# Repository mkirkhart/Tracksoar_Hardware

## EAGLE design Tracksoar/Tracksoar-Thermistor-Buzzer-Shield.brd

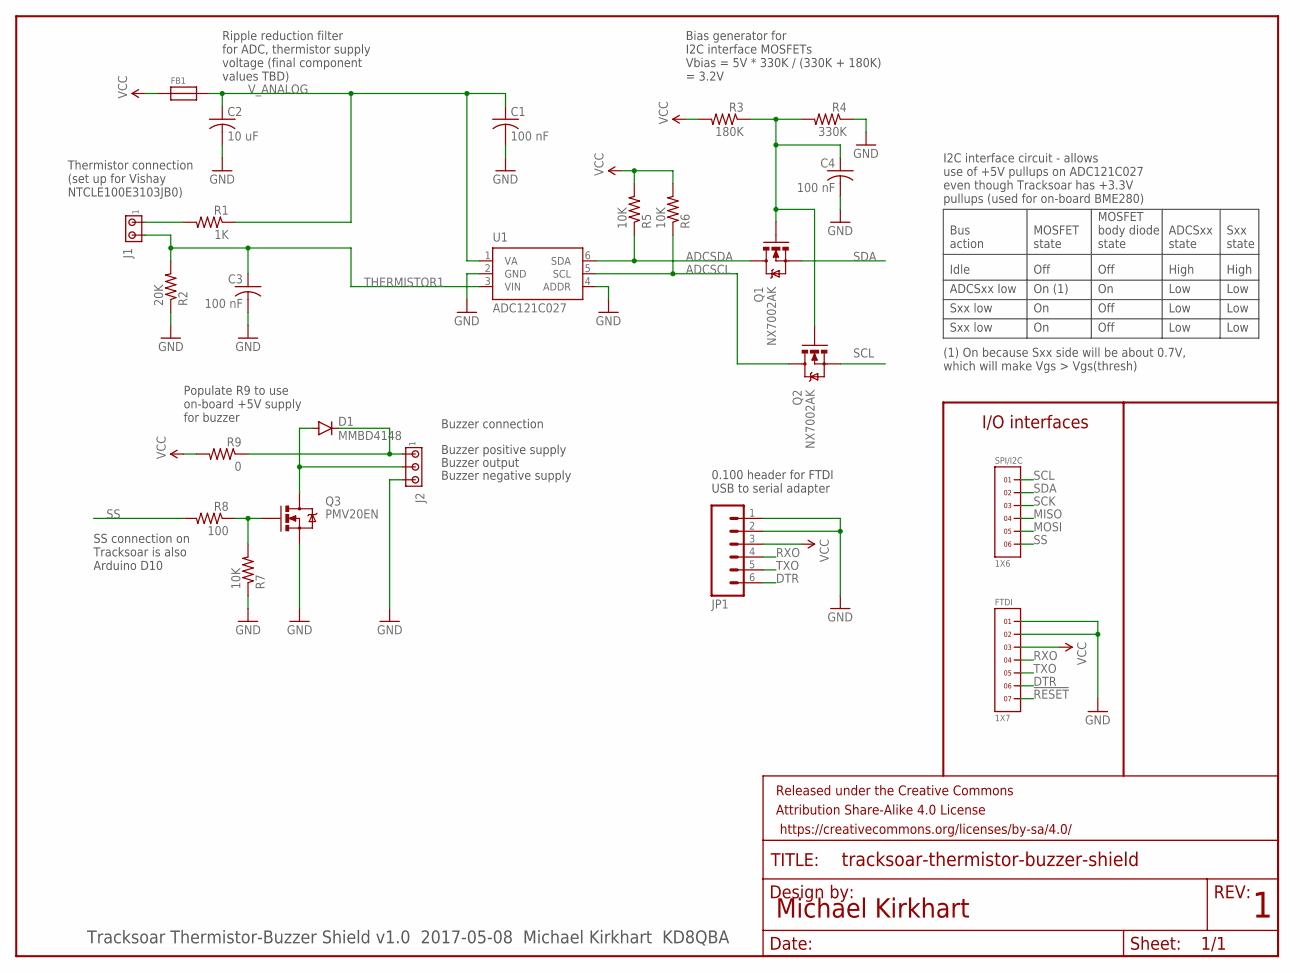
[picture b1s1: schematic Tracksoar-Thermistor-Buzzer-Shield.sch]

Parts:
C1, C3, C4: 100 nF; C0805
C2: 10 uF; C0805
D1: MMBD4148; SOT23-3
FB1: FERRITE0805; 0805
FRAME1: FRAME-LETTER; CREATIVE_COMMONS
FTDI: 1X7
J1: MTA02-100; 10X02MTA
J2: MTA03-100; 10X03MTA
JP1: M06SILK_FEMALE_PTH; 1X06
Q1, Q2: NX7002AK; SOT23-3
Q3: PMV20EN; SOT23-3
R1: 1K; R0805
R2: 20K; R0805
R3: 180K; R0805
R4: 330K; R0805
R5, R6, R7: 10K; R0805
R8: 100; R0805
R9: 0; R0805
SPI/I2C: 1X6
U1: ADC121C027; SOT23-6

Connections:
!RESET: FTDI.7
ADCSCL: Q2.3 (D), R6.1, U1.5 (SCL)
ADCSDA: Q1.3 (D), R5.1, U1.6 (SDA)
DTR: FTDI.6, JP1.6
GND: C1.2, C2.2, C3.2, C4.2, FTDI.1, FTDI.2, J2.3, JP1.1, JP1.2, Q3.2 (S), R2.1, R4.1, R7.1, U1.2 (GND), U1.4 (ADDR)
MISO: SPI/I2C.4
MOSI: SPI/I2C.5
unnamed: C4.1, Q1.1 (G), Q2.1 (G), R3.1, R4.2
unnamed: Q3.1 (G), R7.2, R8.1
unnamed: J1.1, R1.2
unnamed: D1.1 (A), J2.2, Q3.3 (D)
unnamed: D1.3 (C), J2.1, R9.1
RXO: FTDI.4, JP1.4
SCK: SPI/I2C.3
SCL: Q2.2 (S), SPI/I2C.1
SDA: Q1.2 (S), SPI/I2C.2
SS: R8.2, SPI/I2C.6
THERMISTOR1: C3.1, J1.2, R2.2, U1.3 (VIN)
TXO: FTDI.5, JP1.5
VCC: FB1.1, FTDI.3, JP1.3, R3.2, R5.2, R6.2, R9.2
V_ANALOG: C1.1, C2.1, FB1.2, R1.1, U1.1 (VA)

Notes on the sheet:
Michael Kirkhart
I/O interfaces
Tracksoar Thermistor-Buzzer Shield v1.0 2017-05-08 Michael Kirkhart KD8QBA
Buzzer positive supply
Buzzer output
Buzzer negative supply
0.100 header for FTDI USB to serial adapter
Thermistor connection (set up for Vishay NTCLE100E3103JB0)
Buzzer connection
SS connection on Tracksoar is also Arduino D10
Bias generator for I2C interface MOSFETs Vbias = 5V * 330K / (330K + 180K) = 3.2V
I2C interface circuit - allows use of +5V pullups on ADC121C027 even though Tracksoar has +3.3V pullups (used for on-board BME280)
MOSFET state
Sxx state
MOSFET body diode state
Idle
ADCSxx low
Sxx low
Off
Bus action
ADCSxx state
On (1)
High
Low
(1) On because Sxx side will be about 0.7V, which will make Vgs > Vgs(thresh)
Ripple reduction filter for ADC, thermistor supply voltage (final component values TBD)
Populate R9 to use on-board +5V supply for buzzer

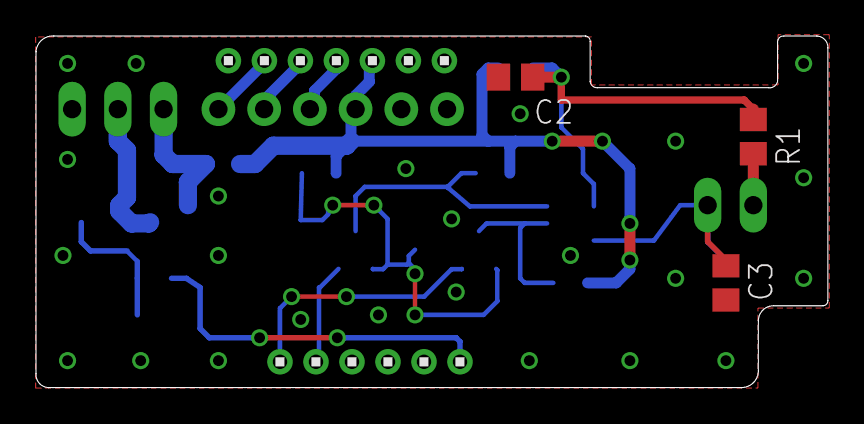
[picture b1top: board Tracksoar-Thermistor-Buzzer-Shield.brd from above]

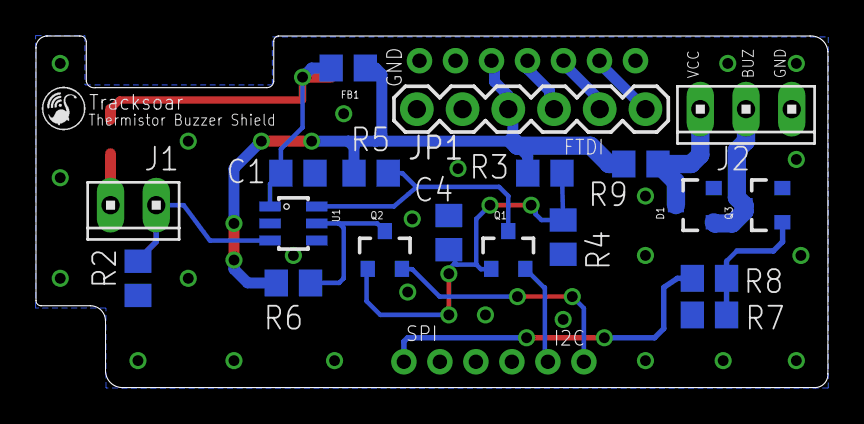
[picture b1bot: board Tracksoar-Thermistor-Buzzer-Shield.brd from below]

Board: 2 copper layers, 44.0 x 19.5 mm, 25 parts (19 on the bottom side), 17 nets.

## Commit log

2017-05-14 Adding v1.0 Tracksoar Thermistor-Buzzer shield * Thermistor-Buzzer shield provides the following capabilities: * 1. Analog interface for an NTC type thermistor using an I2C interface ADC * 2. Low sid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

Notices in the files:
parts and their libraries:
SparkFun-Aesthetics: Licensing: Creative Commons ShareAlike 4.0 International - https://creativecommons.org/licenses/by-sa/4.0
SparkFun-Aesthetics: Released under the Creative Commons Attribution Share-Alike 4.0 License
SparkFun-Aesthetics: https://creativecommons.org/licenses/by-sa/4.0
